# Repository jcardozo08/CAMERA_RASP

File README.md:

# CAMERA_RASP

Placa de interface que se encaixa no **Raspberry Pi Zero 2W** para formar a câmera de bordo do foguete ([RaspCAM](https://github.com/jcardozo08/RaspCAM)). Ela cuida do **gerenciamento de energia**, dos **sensores de telemetria** e dos **avisos sonoros**, deixando o Raspberry livre para gravar o vídeo.

## Destaques

- Encaixe direto no header **2x20** do Raspberry Pi
- **Gerenciamento de energia:** chave ON/OFF, chaveamento por MOSFET P controlado pelo Raspberry (desligamento seguro), diodos Schottky 1N5819 para proteção/ORing e bypass de alimentação
- **Telemetria:** conector para IMU/barômetro (GY-91 / ICM-20948) e microfone I2S INMP441
- **Avisos sonoros** por buzzer acionado com transistor
- Porta **USB-A** para a câmera e proteções ESD/TVS

| Topo | Base |
|:---:|:---:|
|  |  |

## Arquivos

- `CAMERA_RASP.kicad_sch`: esquemático ([ver em SVG](images/schematic.svg))
- `CAMERA_RASP.kicad_pcb`: layout da placa ([ver em SVG](images/layout.svg))
- `CAMERA_RASP.step`: modelo 3D

**Ferramenta:** KiCad

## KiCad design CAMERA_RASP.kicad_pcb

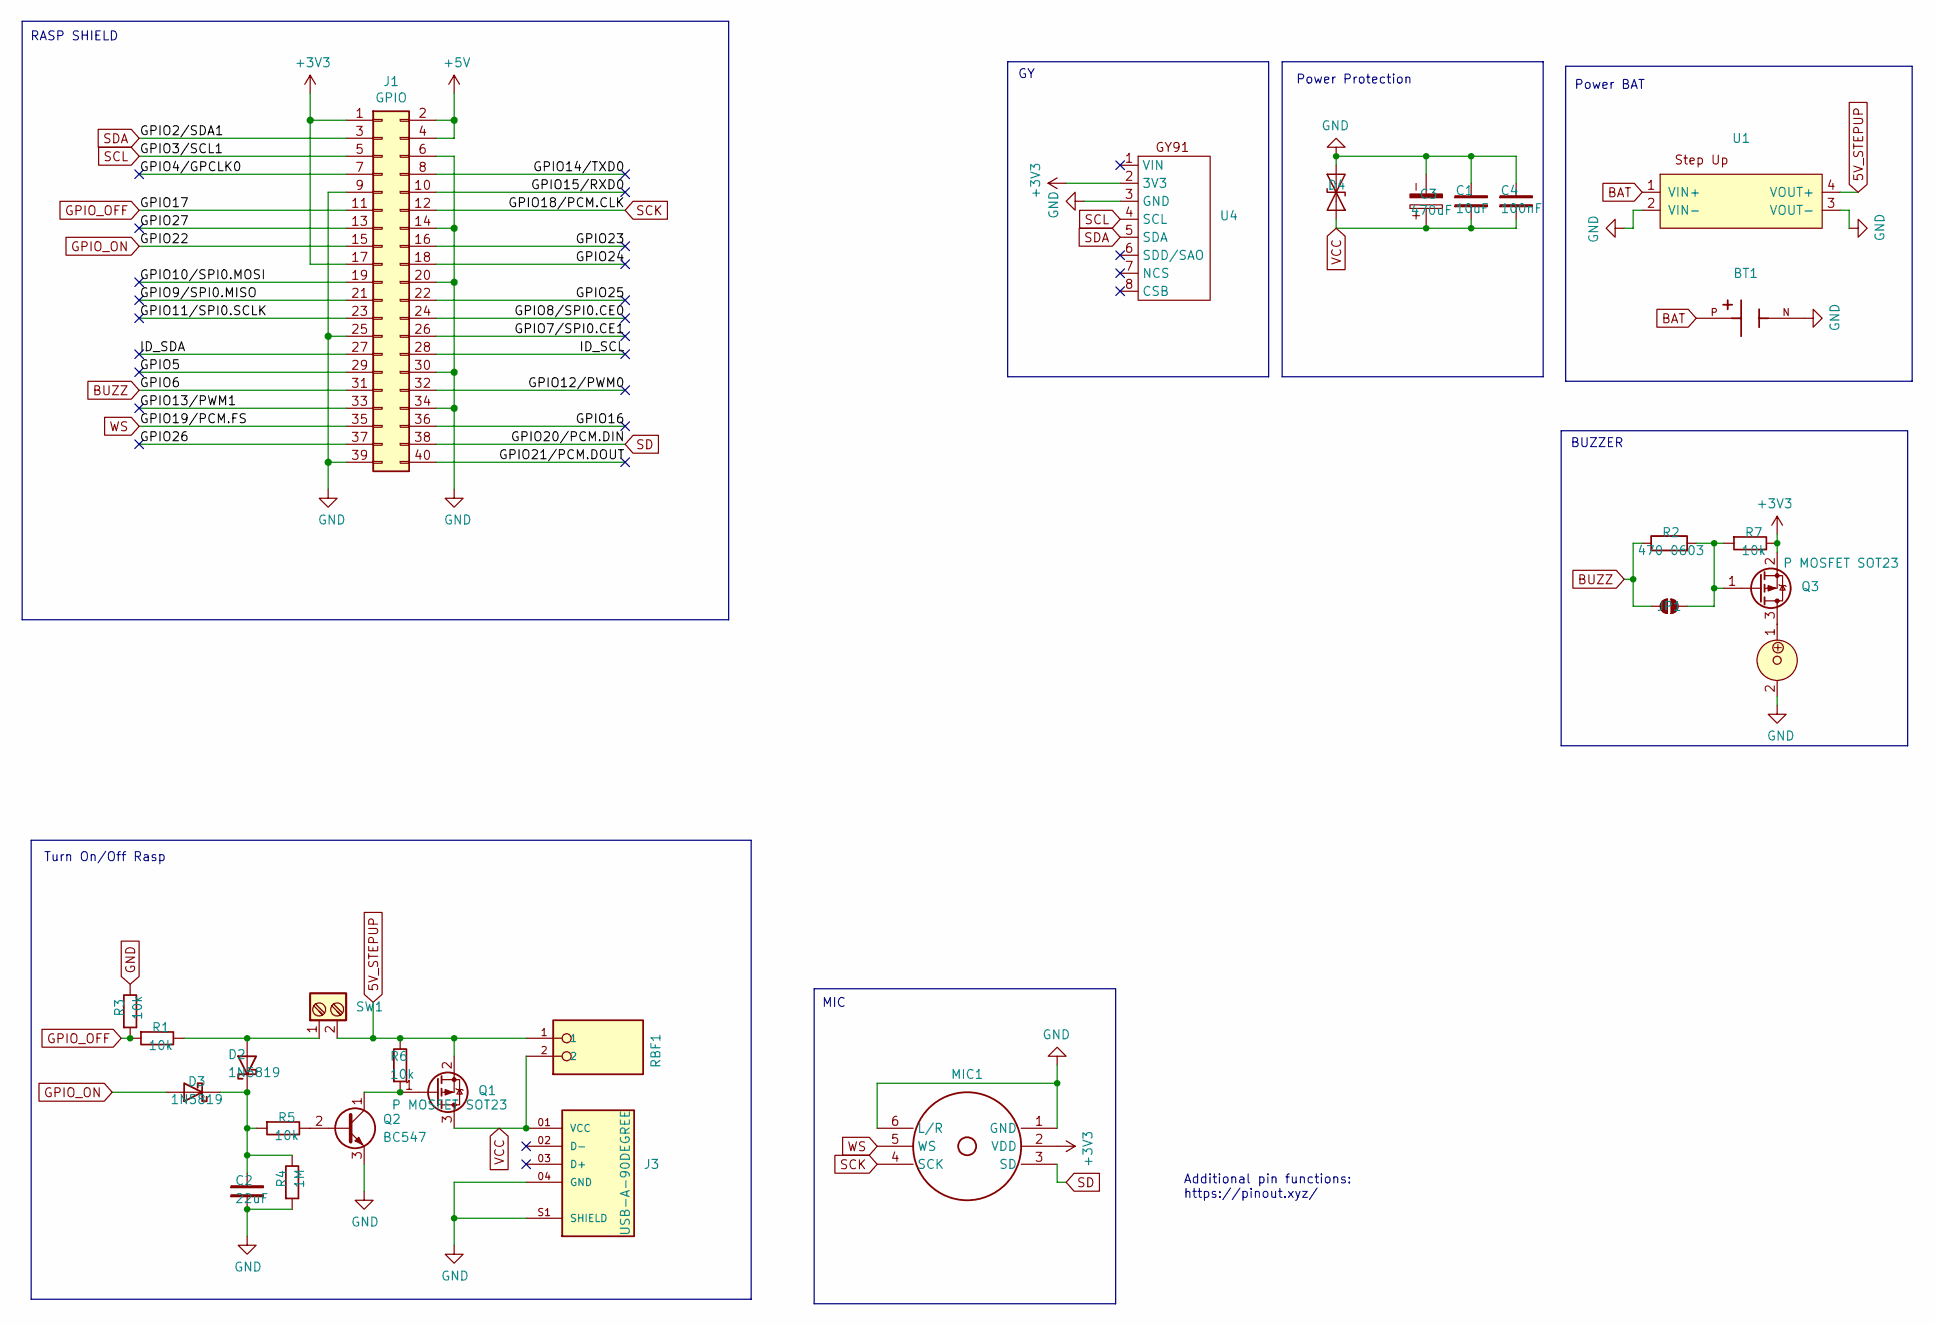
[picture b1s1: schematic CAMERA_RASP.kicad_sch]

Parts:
B1: SW1; Borne 2 Vias
BT1: 18650_SMD
C1: 10uF; C_0805_2012Metric_Pad1.18x1.45mm_HandSolder
C2: 22uF; C_0805_2012Metric_Pad1.18x1.45mm_HandSolder
C3: 470uF; CP_Radial_D8.0mm_P3.50mm
C4: 100nF; C_0805_2012Metric_Pad1.18x1.45mm_HandSolder
D2, D3: 1N5819; D_DO-41_SOD81_P10.16mm_Horizontal
D4: PESD15VL1BA; D_SOD-323
J1: GPIO; PinSocket_2x20_P2.54mm_Vertical
J3: USB-A-90DEGREE; PARTREV R
JP1: Jumper_2_NO
MIC1: MIC_INMP441
Q1, Q3: P MOSFET SOT23; SOT-23
Q2: BC547; TO-92L_Inline_Wide
R1, R3, R5, R6, R7: 10k; R_Axial_DIN0207_L6.3mm_D2.5mm_P10.16mm_Horizontal
R2: 470 0603; R_0603_1608Metric_Pad0.98x0.95mm_HandSolder
R4: 1M; R_Axial_DIN0207_L6.3mm_D2.5mm_P10.16mm_Horizontal
RBF1: MiniBorne2Vias; PARTREV 03.03.2021
U1: Step Up
U4: GY-91_Module
U7: Buzzer

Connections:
5V_STEPUP: B1.2, Q1.2 (S), R6.2, RBF1.1, U1.4 (VOUT+)
+3V3: J1.1, J1.17, MIC1.2 (VDD), Q3.2 (S), R7.2, U4.2 (3V3)
+5V: J1.2, J1.4
/GPIO4/GPCLK0: J1.7
/GPIO5: J1.29
/GPIO7/SPI0.CE1: J1.26
/GPIO8/SPI0.CE0: J1.24
/GPIO9/SPI0.MISO: J1.21
/GPIO10/SPI0.MOSI: J1.19
/GPIO11/SPI0.SCLK: J1.23
/GPIO12/PWM0: J1.32
/GPIO13/PWM1: J1.33
/GPIO14/TXD0: J1.8
/GPIO15/RXD0: J1.10
/GPIO16: J1.36
/GPIO21/PCM.DOUT: J1.40
/GPIO23: J1.16
/GPIO24: J1.18
/GPIO25: J1.22
/GPIO26: J1.37
/GPIO27: J1.13
/ID_SCL: J1.28
/ID_SDA: J1.27
BAT: BT1.P, U1.1 (VIN+)
BUZZ: J1.31, JP1.1 (A), R2.1
GND: BT1.N, C1.2, C2.1, C3.2, C4.2, D4.2 (A2), J1.6, J1.9, J1.14, J1.20, J1.25, J1.30, J1.34, J1.39, J3.04 (GND), J3.S1 (SHIELD), J3.S2 (SHIELD), MIC1.1 (GND), MIC1.6 (L/R), Q2.3 (E), R3.2, R4.1, U1.2 (VIN-), U1.3 (VOUT-), U4.3 (GND), U7.2
GPIO_OFF: J1.11, R1.1, R3.1
GPIO_ON: D3.2 (A), J1.15
unnamed: B1.1, D2.2 (A), R1.2
unnamed: C2.2, D2.1 (K), D3.1 (K), R4.2, R5.1
unnamed: JP1.2 (B), Q3.1 (G), R2.2, R7.1
unnamed: Q1.1 (G), Q2.1 (C), R6.1
unnamed: Q2.2 (B), R5.2
unnamed: Q3.3 (D), U7.1
SCK: J1.12, MIC1.4 (SCK)
SCL: J1.5, U4.4 (SCL)
SD: J1.38, MIC1.3 (SD)
SDA: J1.3, U4.5 (SDA)
VCC: C1.1, C3.1, C4.1, D4.1 (A1), J3.01 (VCC), Q1.3 (D), RBF1.2
WS: J1.35, MIC1.5 (WS)

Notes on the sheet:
BUZZER
Turn On/Off Rasp
Power BAT
RASP SHIELD
MIC
Additional pin functions: https://pinout.xyz/
Power Protection

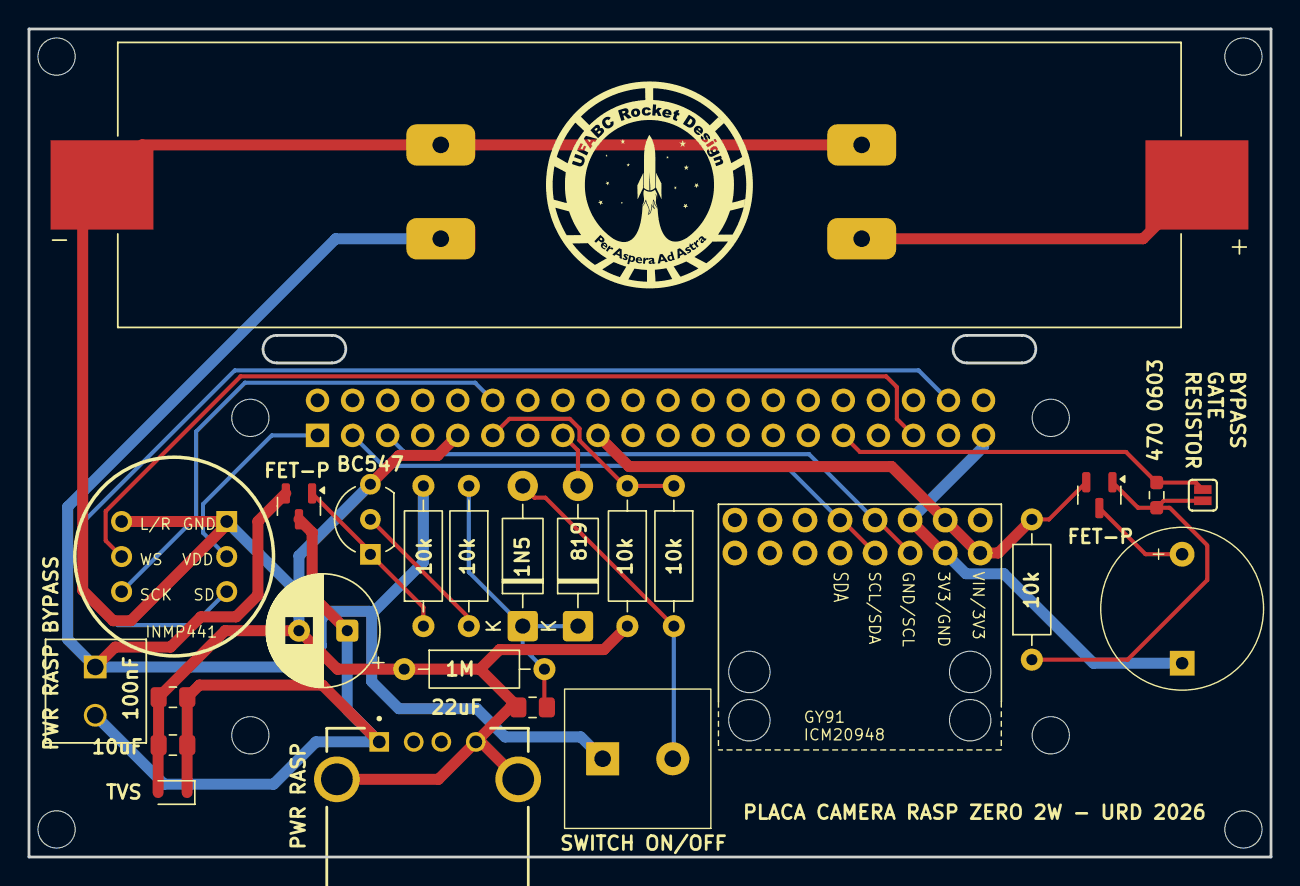
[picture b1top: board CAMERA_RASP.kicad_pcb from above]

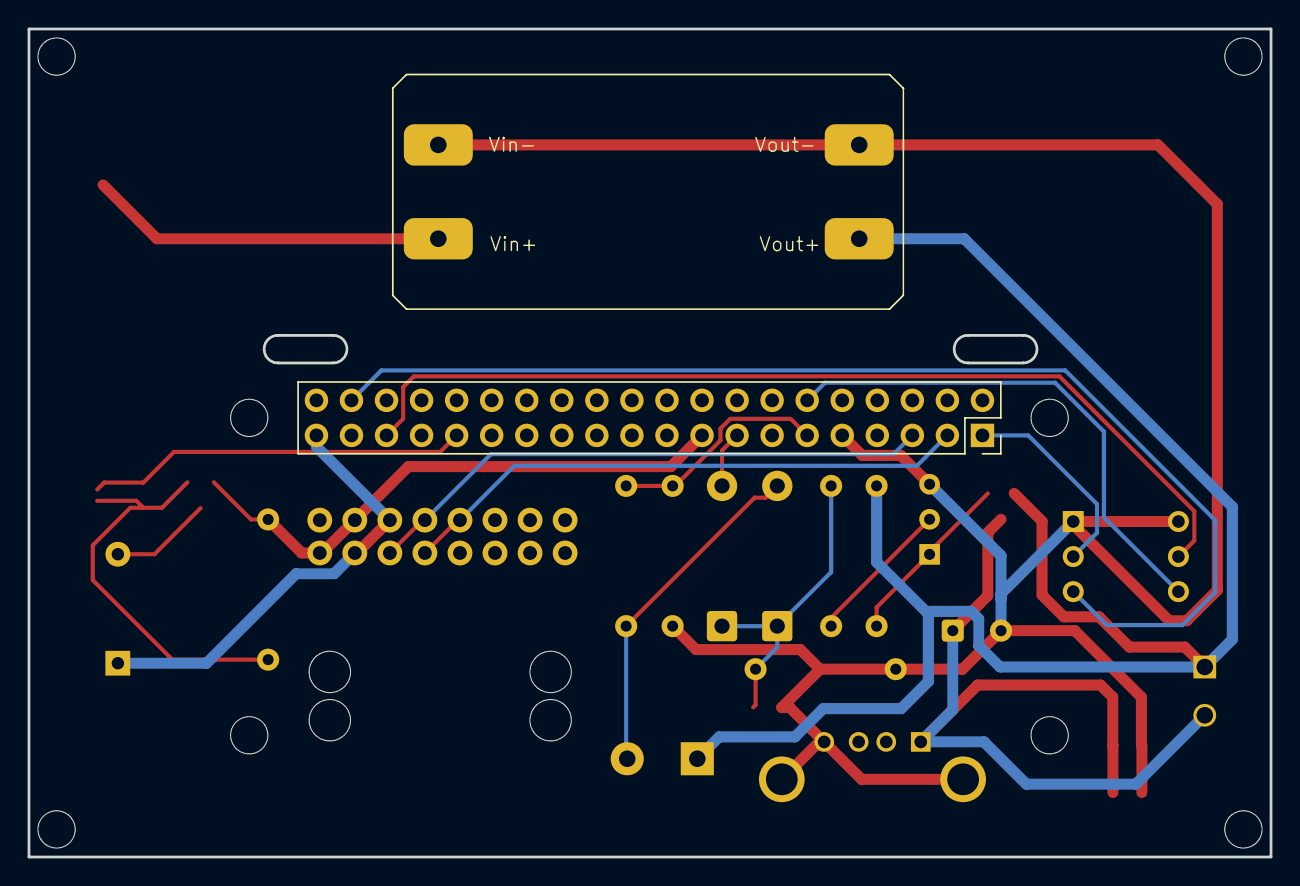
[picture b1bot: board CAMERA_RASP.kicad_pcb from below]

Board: 2 copper layers, 90.0 x 60.0 mm, 36 parts (2 on the bottom side), 20 nets.

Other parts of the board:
3, 4, 5, 6: (no value)
G1: LOGO; LogoRocket
MH1, MH2, MH3, MH4: MountingHole_2.7mm_M2.5
